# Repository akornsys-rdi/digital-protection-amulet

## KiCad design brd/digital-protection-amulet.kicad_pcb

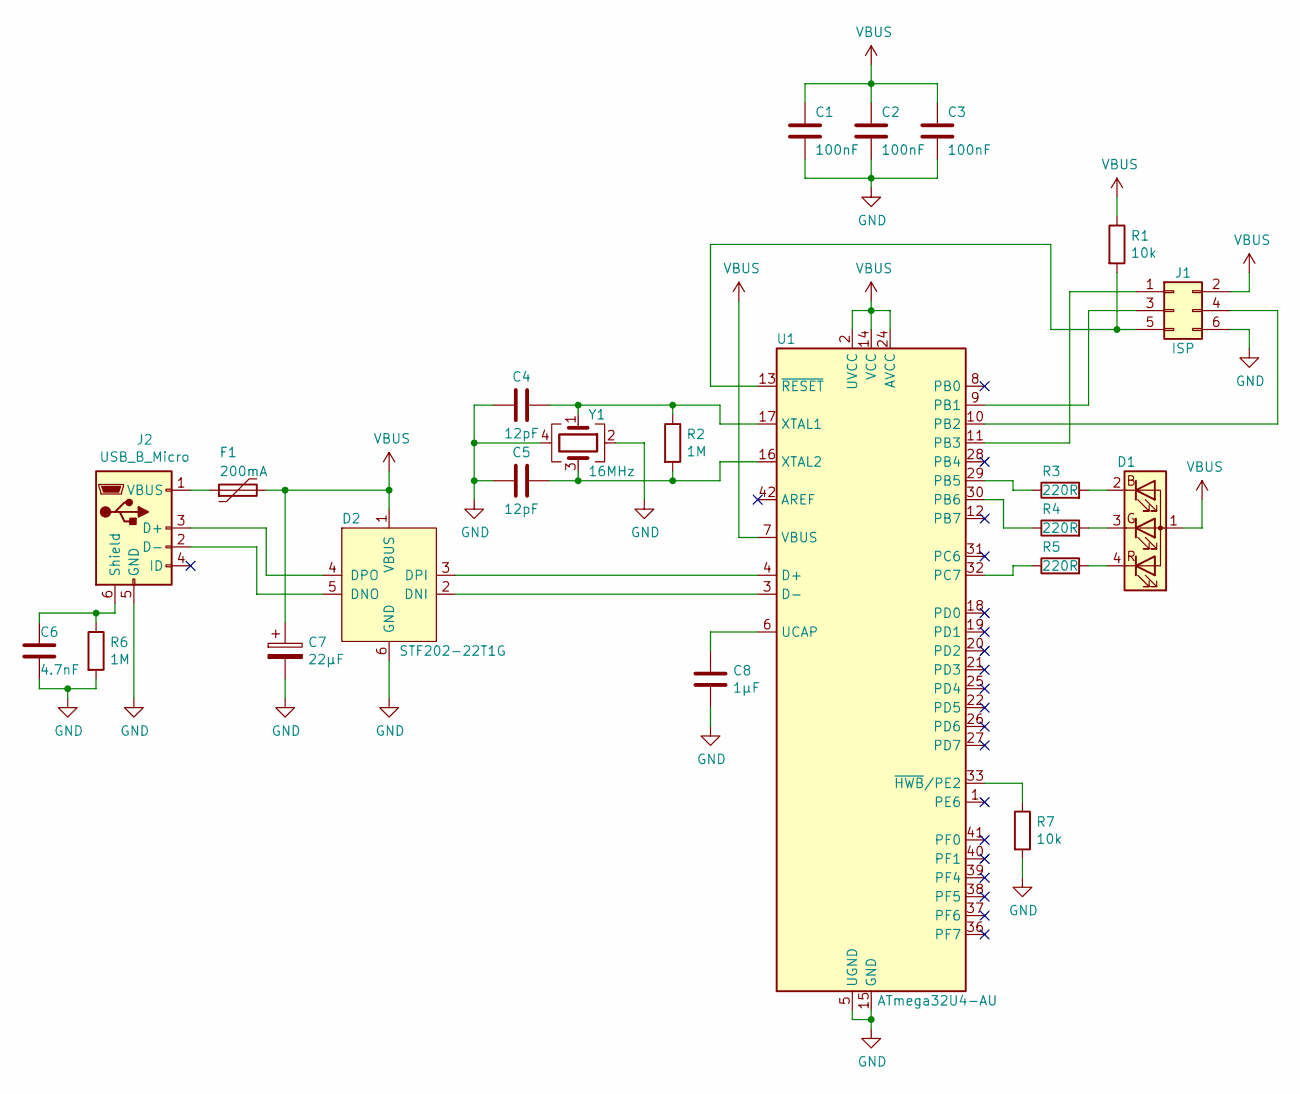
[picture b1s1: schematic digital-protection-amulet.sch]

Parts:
C1, C2, C3: 100nF; C_0805_2012Metric; Manufacturer Part Number C0805C104M5RACTU
C4, C5: 12pF; C_0805_2012Metric; Manufacturer Part Number CC0805JRNPO9BN120
C6: 4.7nF; C_0805_2012Metric; Manufacturer Part Number C0805C472K5RACTU
C7: 22µF; CP_EIA-3216-18_Kemet-A; Manufacturer Part Number TAJA226M010RNJ
C8: 1µF; C_0805_2012Metric; Manufacturer Part Number CL21B105KOFNNNG
D1: CLMVC-FKC; LED_Cree-PLCC4_2x2mm_CW; Manufacturer Part Number CLMVC-FKC-CGJJM569aBB7a343
D2: STF202-22T1G; TSOP-6_1.65x3.05mm_P0.95mm; Manufacturer Part Number STF202-22T1G
F1: 200mA; Fuse_1210_3225Metric_Castellated; Manufacturer Part Number 0ZCH0020FF2E
J1: ISP; IDC-Header_2x03_P2.54mm_Vertical
J2: USB_B_Micro; USB_Micro-B_Amphenol_10118194_Horizontal; Manufacturer Part Number 10118194-0001LF
R1, R7: 10k; R_0805_2012Metric; Manufacturer Part Number CR0805-JW-103ELF
R2, R6: 1M; R_0805_2012Metric; Manufacturer Part Number CR0805-JW-105ELF
R3, R4, R5: 220R; R_0805_2012Metric; Manufacturer Part Number CR0805-JW-221ELF
U1: ATmega32U4-AU; TQFP-44_10x10mm_P0.8mm; Manufacturer Part Number ATMEGA32U4-AU
Y1: 16MHz; Crystal_SMD_EuroQuartz_X22-4Pin_2.5x2.0mm; Manufacturer Part Number ECS-160-8-36CKM-TR3

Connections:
GND: C1.2, C2.2, C3.2, C4.2, C5.2, C6.2, C7.2, C8.2, D2.6 (GND), J1.6, J2.5 (GND), R6.2, R7.2, U1.5 (UGND), U1.15 (GND), U1.23 (GND), U1.35 (GND), U1.43 (GND), Y1.2, Y1.4
unnamed: C4.1, R2.1, U1.17 (XTAL1), Y1.1
unnamed: C5.1, R2.2, U1.16 (XTAL2), Y1.3
unnamed: C6.1, J2.6 (Shield), R6.1
unnamed: C8.1, U1.6 (UCAP)
unnamed: D1.2 (BK), R3.2
unnamed: D1.3 (GK), R4.2
unnamed: D1.4 (RK), R5.2
unnamed: D2.2 (DNI), U1.3 (D-)
unnamed: D2.3 (DPI), U1.4 (D+)
unnamed: D2.4 (DPO), J2.3 (D+)
unnamed: D2.5 (DNO), J2.2 (D-)
unnamed: F1.1, J2.1 (VBUS)
unnamed: J1.1, U1.11 (PB3)
unnamed: J1.3, U1.9 (PB1)
unnamed: J1.4, U1.10 (PB2)
unnamed: J1.5, R1.2, U1.13 (~RESET)
unnamed: R3.1, U1.29 (PB5)
unnamed: R4.1, U1.30 (PB6)
unnamed: R5.1, U1.32 (PC7)
unnamed: R7.1, U1.33 (~HWB~/PE2)
VBUS: C1.1, C2.1, C3.1, C7.1, D1.1 (A), D2.1 (VBUS), F1.2, J1.2, R1.1, U1.2 (UVCC), U1.7 (VBUS), U1.14 (VCC), U1.24 (AVCC), U1.34 (VCC), U1.44 (AVCC)

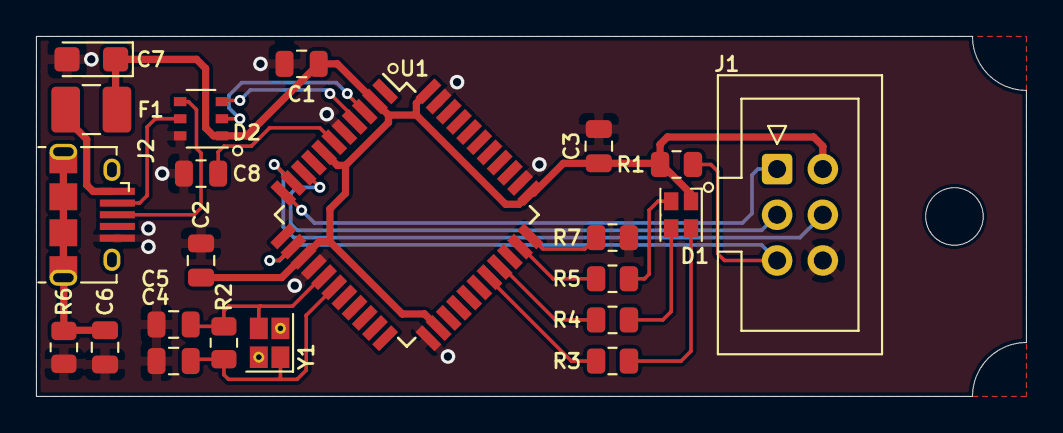
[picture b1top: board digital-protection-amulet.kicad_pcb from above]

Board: 2 copper layers, 55.0 x 20.0 mm, 22 parts (0 on the bottom side), 22 nets.

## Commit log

2023-05-14 unique version for Patri
2023-05-15 cambiado registro epoch para resolver Y2038
2023-05-15 typo
2023-05-16 actualizado mapa eeprom
2023-05-30 mapa eeprom actualizado

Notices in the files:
brd/digital-protection-amulet.kicad_pcb:
Copyright © 2023 RileyStarlight
Released under CERN OHL-S 2 License
https://cern-ohl.web.cern.ch
